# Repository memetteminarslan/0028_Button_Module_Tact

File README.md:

# 0028_Button_Module_Tact
You are seeing a large number of widely used button modules in electronic development kits. More information coming soon...

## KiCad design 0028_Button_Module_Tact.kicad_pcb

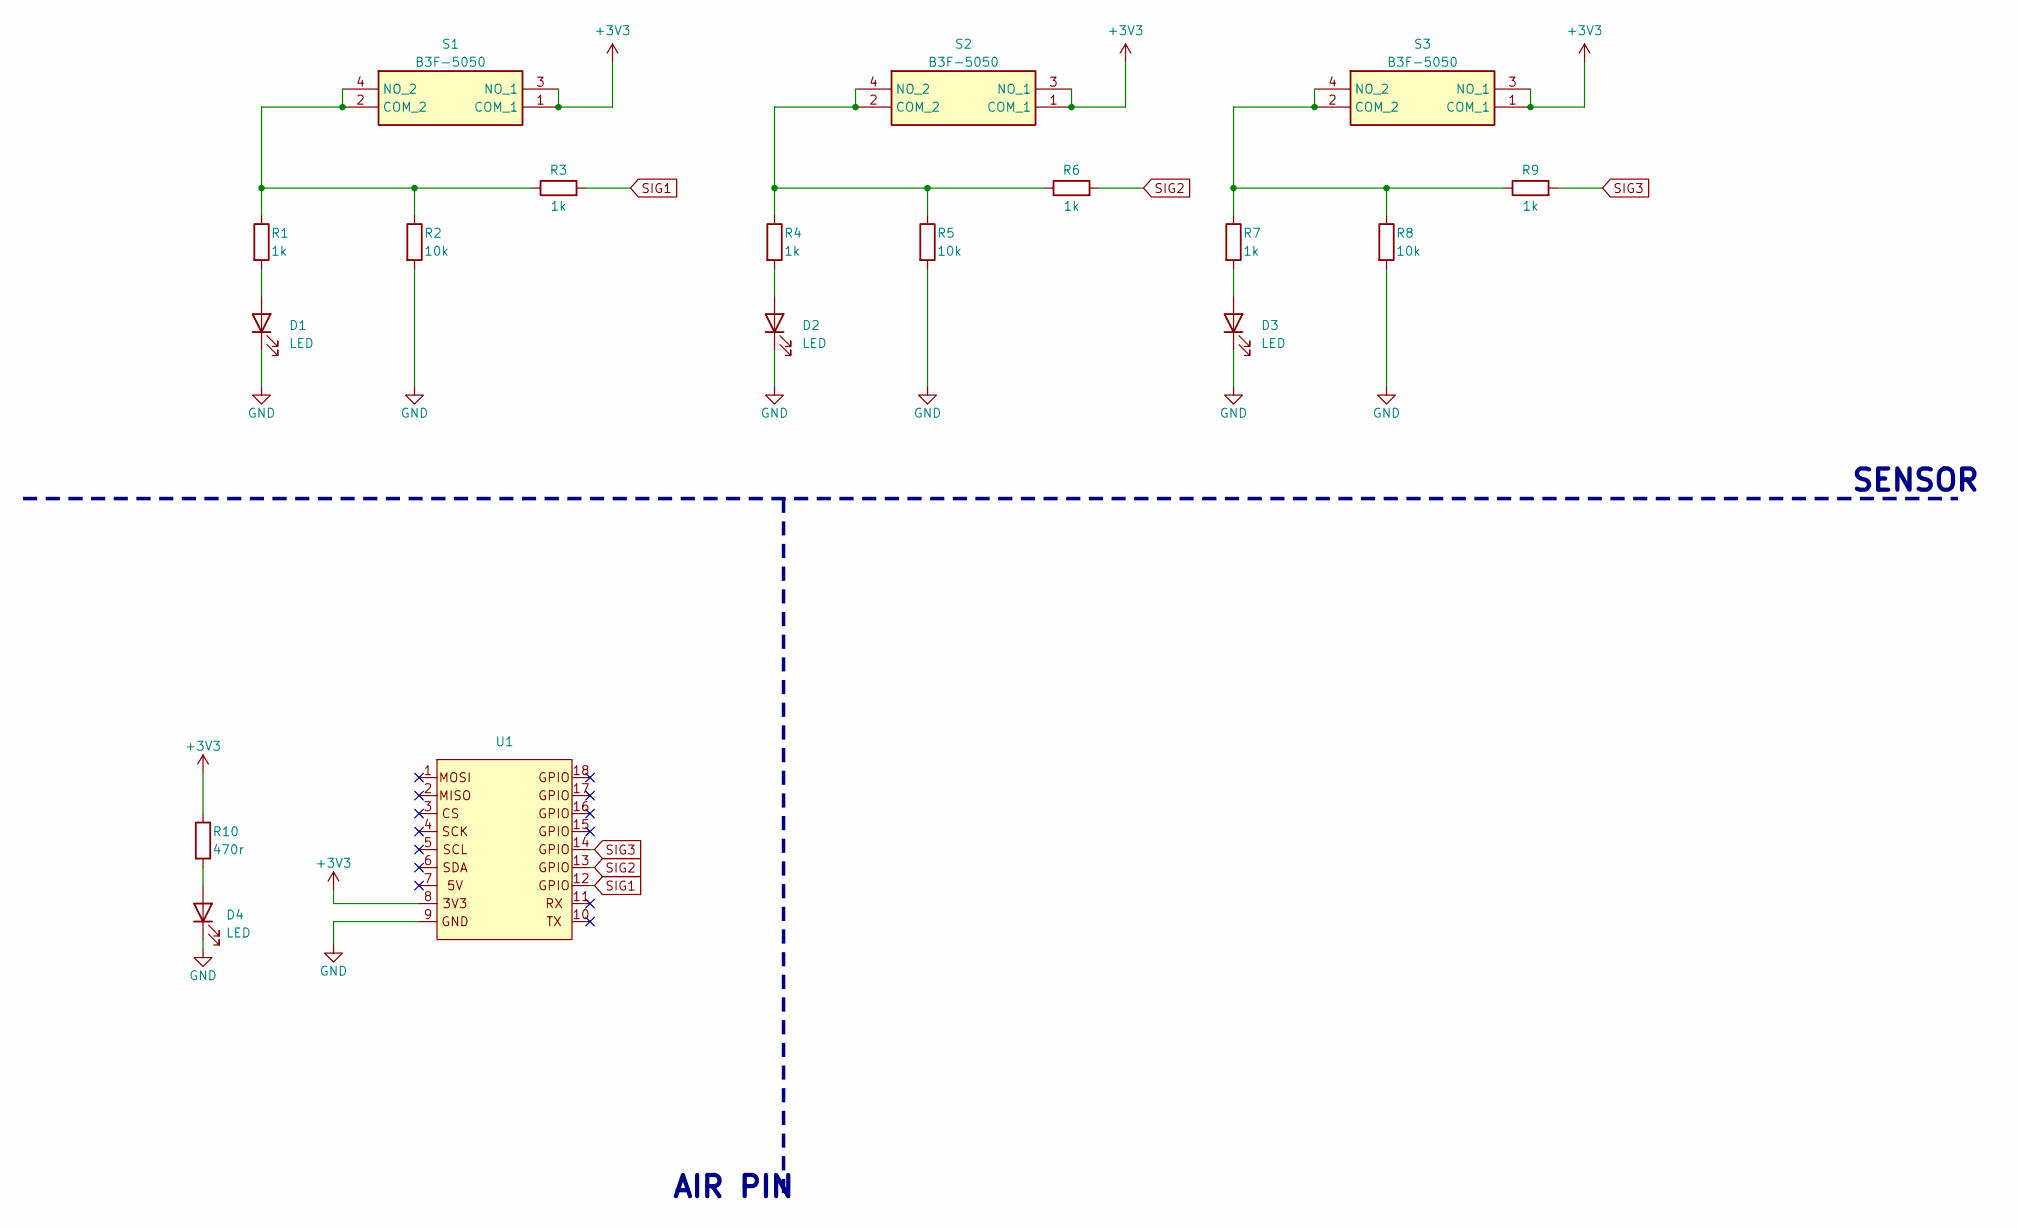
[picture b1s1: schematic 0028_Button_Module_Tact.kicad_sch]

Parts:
D1, D2, D3, D4: LED; LED_0603_1608Metric
R1, R3, R4, R6, R7, R9: 1k; R_0603_1608Metric
R2, R5, R8: 10k; R_0603_1608Metric
R10: 470r; R_0603_1608Metric
S1, S2, S3: B3F-5050; B3F-4055; Mouser Part Number 653-B3F-5050
U1: pin_header_5-3

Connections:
+3V3: R10.1, S1.1 (COM_1), S1.3 (NO_1), S2.1 (COM_1), S2.3 (NO_1), S3.1 (COM_1), S3.3 (NO_1), U1.8
GND: D1.1 (K), D2.1 (K), D3.1 (K), D4.1 (K), R2.2, R5.2, R8.2, U1.9
unnamed: D1.2 (A), R1.2
unnamed: D2.2 (A), R4.2
unnamed: D3.2 (A), R7.2
unnamed: D4.2 (A), R10.2
unnamed: R1.1, R2.1, R3.1, S1.2 (COM_2), S1.4 (NO_2)
unnamed: R4.1, R5.1, R6.1, S2.2 (COM_2), S2.4 (NO_2)
unnamed: R7.1, R8.1, R9.1, S3.2 (COM_2), S3.4 (NO_2)
SIG1: R3.2, U1.12
SIG2: R6.2, U1.13
SIG3: R9.2, U1.14

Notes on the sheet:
SENSOR
AIR PIN

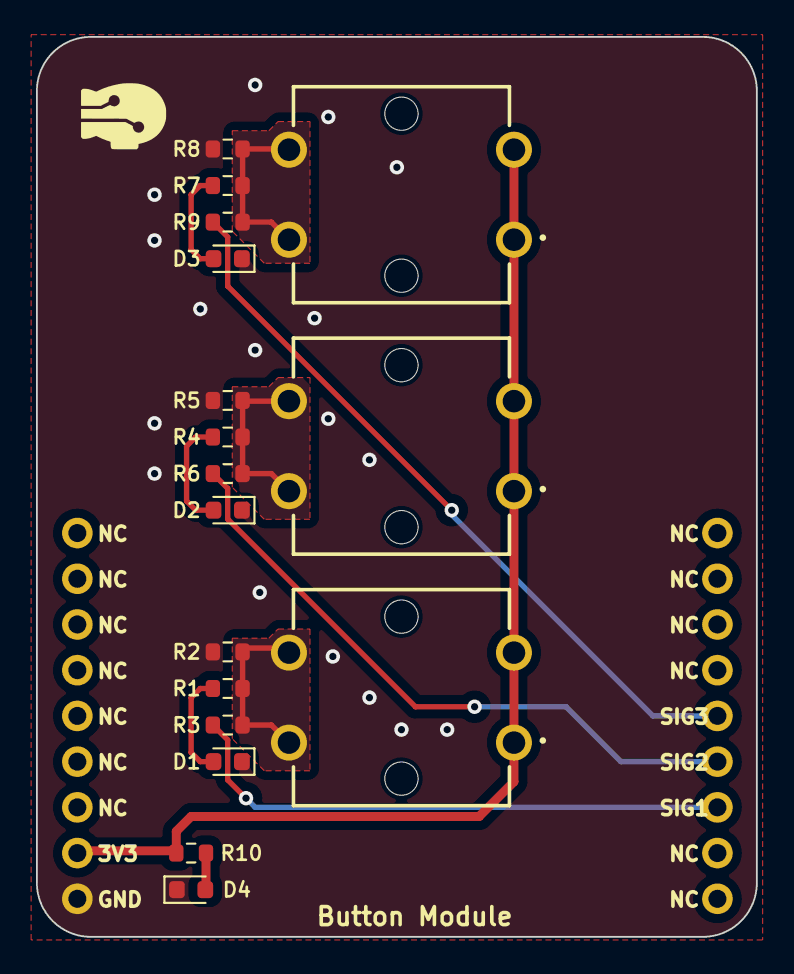
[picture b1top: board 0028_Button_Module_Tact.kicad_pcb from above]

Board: 2 copper layers, 40.0 x 50.0 mm, 18 parts (0 on the bottom side), 12 nets.
